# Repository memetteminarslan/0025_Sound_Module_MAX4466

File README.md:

# 0025_Sound_Module_MAX4466
You are seeing a large number of widely used Sound Module in electronic development kits. More information coming soon...

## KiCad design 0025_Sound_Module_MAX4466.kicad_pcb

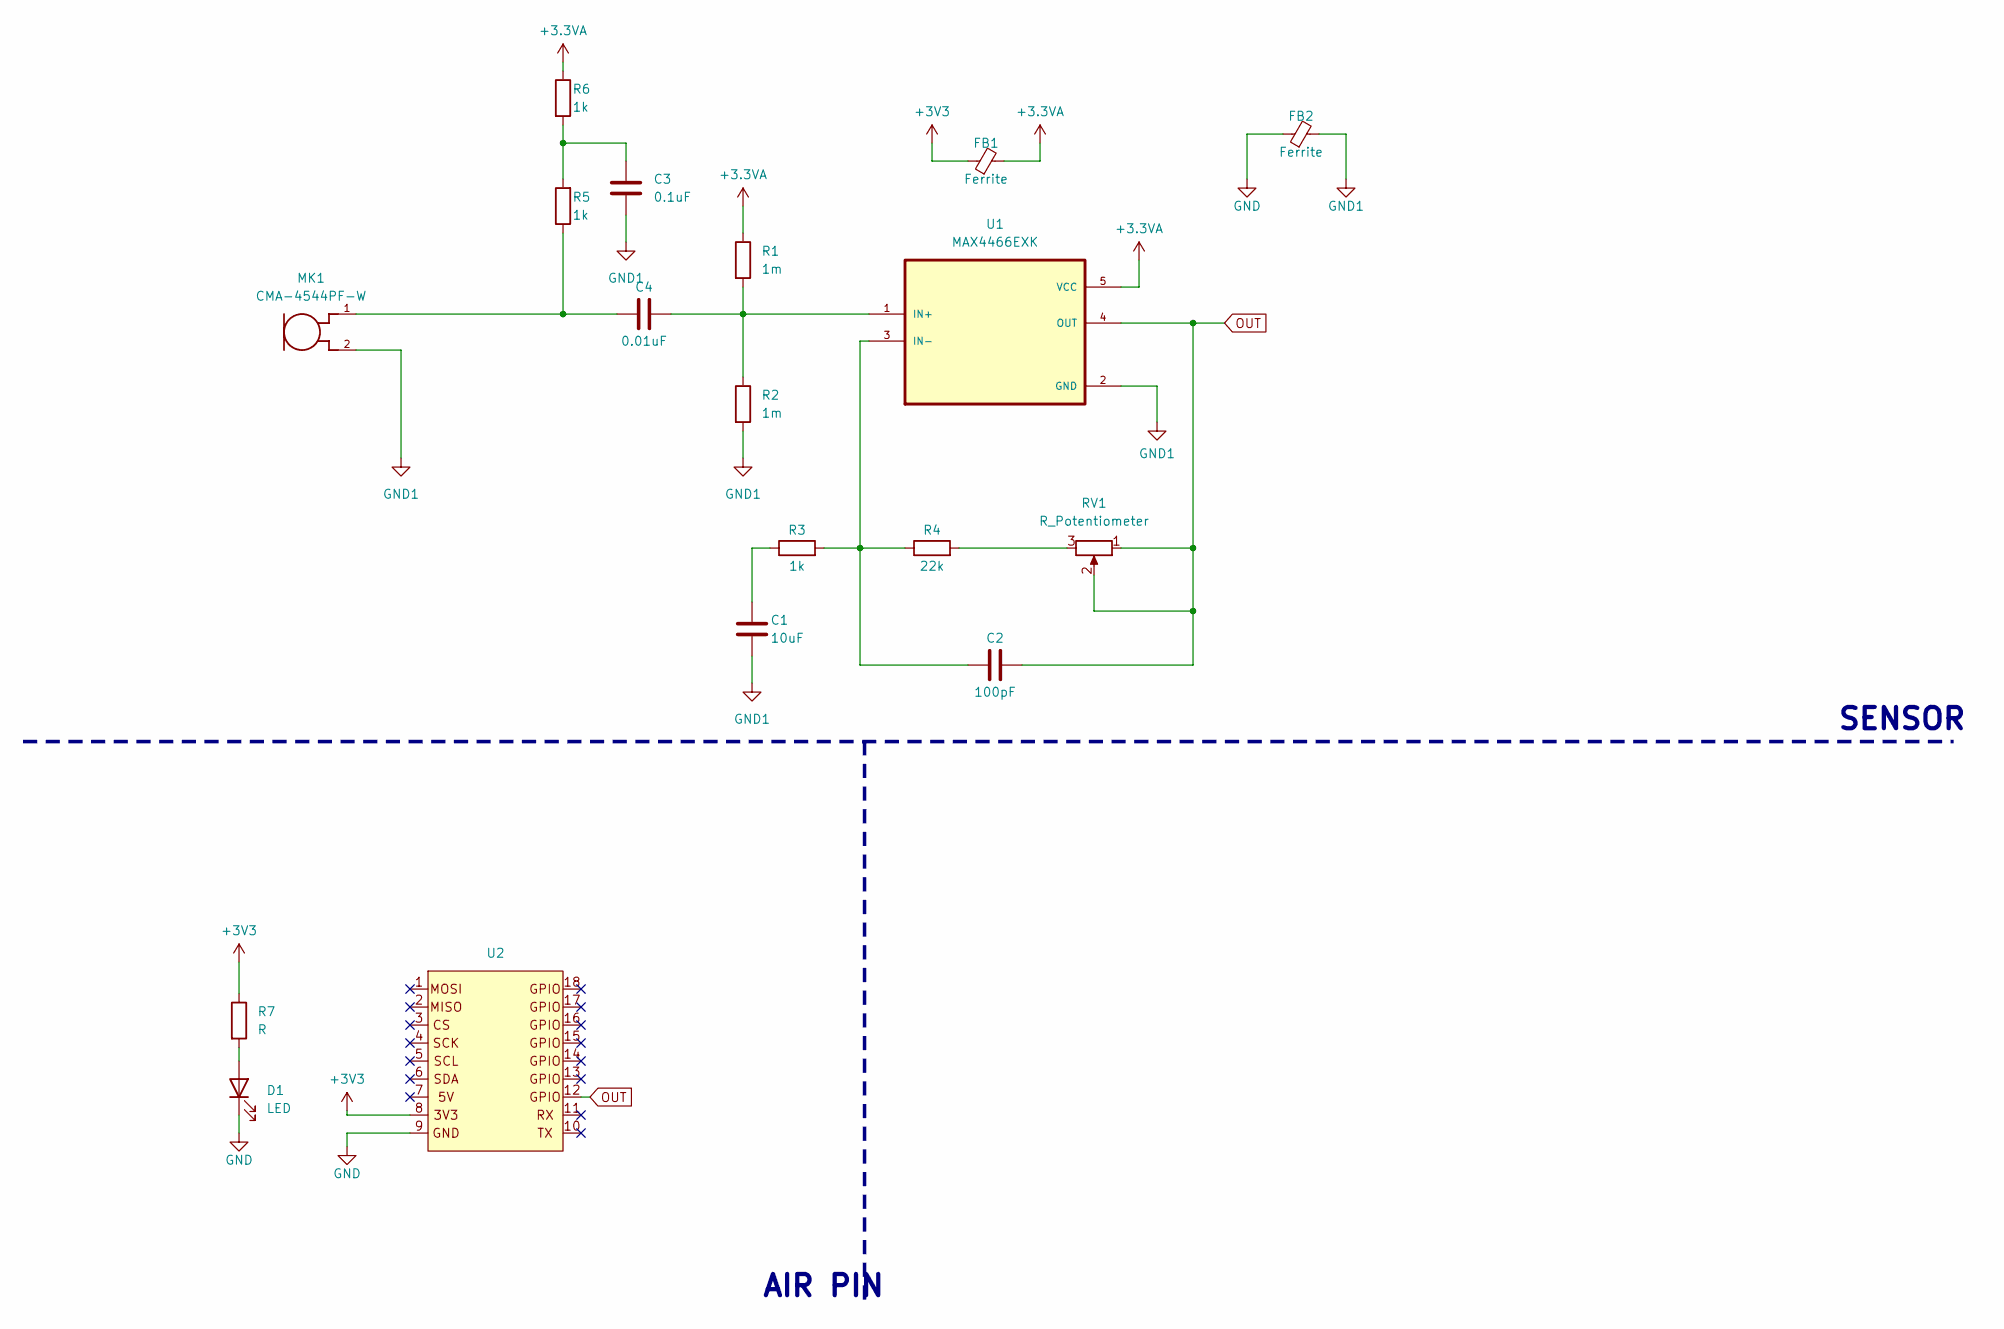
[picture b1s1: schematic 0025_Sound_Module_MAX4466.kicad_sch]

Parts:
C1: 10uF; C_0805_2012Metric
C2: 100pF; C_0805_2012Metric
C3: 0.1uF; C_0805_2012Metric
C4: 0.01uF; C_0805_2012Metric
D1: LED; LED_0805_2012Metric
FB1, FB2: Ferrite; L_0805_2012Metric
MK1: CMA-4544PF-W; MIC_CMA-4544PF-W
R1, R2: 1m; R_0805_2012Metric
R3, R5, R6: 1k; R_0805_2012Metric
R4: 22k; R_0805_2012Metric
R7: R; R_0805_2012Metric
RV1: R_Potentiometer; 3362P_1
U1: MAX4466EXK; SOT65P210X110-5N
U2: pin_header

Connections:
+3.3VA: FB1.2, R1.1, R6.1, U1.5 (VCC)
+3V3: FB1.1, R7.1, U2.8
GND: D1.1 (K), FB2.1, U2.9
GND1: C1.1, C3.1, FB2.2, MK1.2, R2.2, U1.2 (GND)
unnamed: C1.2, R3.1
unnamed: C3.2, R5.2, R6.2
unnamed: C4.2, MK1.1, R5.1
unnamed: D1.2 (A), R7.2
unnamed: R4.2, RV1.3
unnamed: C4.1, R1.2, R2.1, U1.1 (IN+)
unnamed: C2.2, R3.2, R4.1, U1.3 (IN-)
OUT: C2.1, RV1.1, RV1.2, U1.4 (OUT), U2.12

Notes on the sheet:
SENSOR
AIR PIN

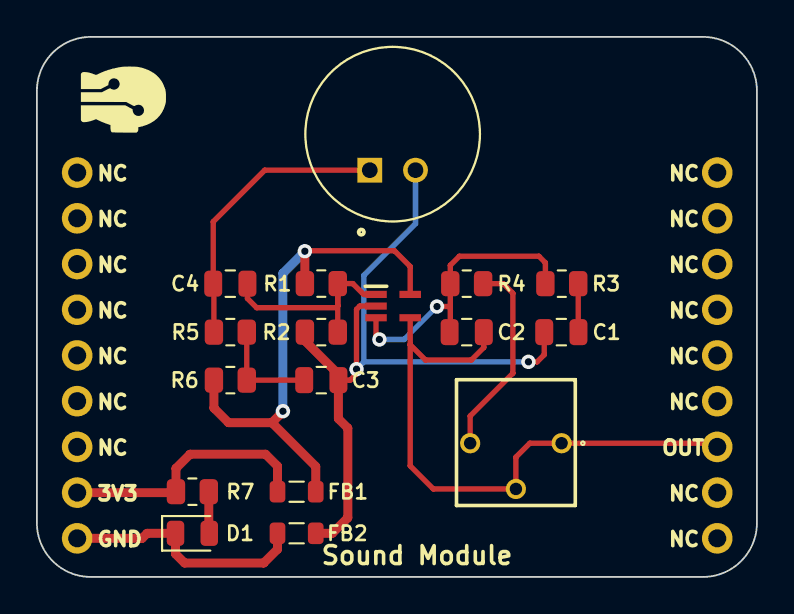
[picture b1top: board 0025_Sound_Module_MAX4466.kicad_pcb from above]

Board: 2 copper layers, 40.0 x 30.0 mm, 18 parts (0 on the bottom side), 12 nets.
